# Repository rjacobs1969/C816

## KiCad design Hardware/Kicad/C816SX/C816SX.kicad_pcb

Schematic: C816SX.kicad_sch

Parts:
C1, C2: 1uF; C_0603_1608Metric
C6, C8: 2.2uF; C_0603_1608Metric
C10, C11: 10uF; C_0805_2012Metric
C22, C23, C24, C25, C26, C27, C28, C29, C30, C31, C32, C33, C34, C35, C36, C37, C38, C39, C40, C41, C42, C43, C44, C45, C48, C49, C50: 100n; C_0402_1005Metric
C46, C47: 2.2n; C_0402_1005Metric
D1: LED; LED_D5.0mm_Horizontal_O6.35mm_Z3.0mm
H5, H6, H7, H8: MountingHole; MountingHole_3.5mm
IC4: IS61WV20488FBLL-10TLI; SOP80P1176X120-44N; Mouser Part Number 870-61W20488FBLL10TI
J1: Conn_02x06_Odd_Even; PinHeader_2x06_P2.54mm_Vertical
J2: HDMI_A; HDMI_A_Molex_208658-1001_Horizontal
J4: USB_A_Stacked; USB_A_Wuerth_61400826021_Horizontal_Stacked
J5, J9: DE9_Pins; DSUB-9_Pins_Horizontal_P2.77x2.84mm_EdgePinOffset4.94mm_Hou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
J10: 5749265-1; 57492651; Mouser Part Number 571-5749265-1
J11: Conn_02x06_Odd_Even; PinSocket_2x06_P2.54mm_Vertical
J14, J15, J19, J20: Conn_02x03_Odd_Even; PinHeader_2x03_P2.54mm_Vertical
J16: Conn_01x06_Pin; PinSocket_1x06_P2.54mm_Vertical
J17: Conn_01x09; PinSocket_1x09_P2.54mm_Vertical
J18: USB_B; USB_B_Lumberg_2411_02_Horizontal
J21: SD_Card_Receptacle; SD_TE_2041021
J22, J23: Conn_01x07_Pin; PinSocket_1x07_P2.54mm_Vertical
J25: Conn_01x02; JST_EH_B2B-EH-A_1x02_P2.50mm_Vertical
J26, J27: NYS354; Mouser Part Number 568-NYS354
NT23, NT24, NT25, NT26, NT27, NT28, NT29, NT30, NT31, NT32, NT33, NT34, NT35, NT36, NT37, NT38, NT39, NT40, NT42, NT43, NT44, NT45, NT48, NT51, NT52, NT53, NT54, NT55, NT56, NT57, NT58, NT59, NT60, NT61, NT62, NT63, NT64, NT65, NT66, NT67, NT68, NT69: NetTie_2; MyNetTie-2_SMD_Pad0.25mm
R15: 3K3; R_0805_2012Metric_Pad1.20x1.40mm_HandSolder
R20, R41, R42, R43, R44: 1K; R_0402_1005Metric
R25, R26, R28, R29, R32, R34: 1k; R_0603_1608Metric
R27: 330; R_0603_1608Metric
R30, R31: 470; R_0603_1608Metric
R33: 330; R_0805_2012Metric_Pad1.20x1.40mm_HandSolder
R35: 1k5; R_0603_1608Metric
RN4, RN6, RN7, RN8, RN9, RN10, RN11, RN12, RN18, RN20: 33; R_Array_Convex_4x0603
RN13, RN14, RN15, RN16, RN19: 10k; R_Array_Convex_4x0603
RN17: 1k; R_Array_Convex_4x0603
SLOT1: DDR3_204P_SMD; DDR3-SMD_0705F0BE40F
SW1: SW_DIP_x04; SW_DIP_SPSTx04_Piano_10.8x11.72mm_W7.62mm_P2.54mm
U1: W65C816SxQ; LQFP-44_10x10mm_P0.8mm
U2: PCM5102A; TSSOP-20_4.4x6.5mm_P0.65mm
U3: XC6206PxxxMR; SOT-23-3
U4, U7: 74LVC07; SOIC-14_3.9x8.7mm_P1.27mm
U8: W65C22SxQ; LQFP-44_10x10mm_P0.8mm
U14: W25Q128JVS; SOIC-8_5.3x5.3mm_P1.27mm
U15, U17, U18, U19, U20, U21, U22: SN74LVC8T245PWR; TSSOP-24_4.4x7.8mm_P0.65mm; LCSC C27643
Y2: SiT8008xx-7x-xxE; Oscillator_SMD_SiT_PQFN-4Pin_2.0x1.6mm

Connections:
+3V3: C23.1, C25.2, C27.1, C29.1, C30.1, C31.1, C40.1, C41.1, C42.1, C48.1, C49.1, C50.1, IC4.11 (VDD_1), IC4.33 (VDD_2), J16.1, J19.1, J20.6, R15.1, R25.2, R26.2, R28.2, R29.1, R34.1, RN17.1 (R1.1), RN17.2 (R2.1), SLOT1.22, SLOT1.24, U2.1 (CPVDD), U2.20 (DVDD), U4.14 (VCC), U7.14 (VCC), U14.8 (VCC), U15.23 (VccB), U15.24 (VccB), U17.23 (VccB), U17.24 (VccB), U18.23 (VccB), U18.24 (VccB), U19.23 (VccB), U19.24 (VccB), U20.23 (VccB), U20.24 (VccB), U22.23 (VccB), U22.24 (VccB), Y2.1 (OE), Y2.4 (Vdd)
/A0: U1.4 (A0), U18.4 (A2), U22.17 (B5)
/A1: U1.5 (A1), U18.6 (A4), U22.16 (B6)
/A2: U1.7 (A2), U18.8 (A6), U22.15 (B7)
/A3: U1.8 (A3), U18.10 (A8), U22.14 (B8)
/A4: U1.9 (A4), U19.3 (A1)
/A5: U1.10 (A5), U19.4 (A2)
/A6: U1.11 (A6), U19.5 (A3)
/A7: U1.12 (A7), U19.6 (A4)
/A8: U1.13 (A8), U19.7 (A5)
/A9: U1.14 (A9), U19.8 (A6)
/A9_IOL27A: SLOT1.148
/A10: U1.15 (A10), U19.9 (A7)
/A11: U1.16 (A11), U19.10 (A8)
/A11_IOL15A: NT36.1, SLOT1.131
/A12: U1.19 (A12), U18.9 (A7)
/A12_IOL13B: NT27.2, SLOT1.123
/A13: U1.20 (A13), U18.7 (A5)
/A13_IOR32A_READY: IC4.38 (A15), SLOT1.98
/A14: U1.21 (A14), U18.5 (A3)
/A14_IOL8B: NT43.2, SLOT1.113
/A15: U1.22 (A15), U18.3 (A1)
/A15_IOL2B: NT42.2, SLOT1.107
/AGND: C1.2, C8.2, C43.2, C46.2, C47.2, J26.MH1, J26.MH2, J26.MH3, J27.MH1, J27.MH2, J27.MH3, NT67.2, U2.9 (AGND), U3.1 (GND)
/AVDD: C1.1, C43.1, U2.8 (AVDD), U3.2 (VO)
/A_0: IC4.4 (A1), NT43.1, RN6.3 (R3.1)
/A_1: IC4.6 (A3), NT44.1, RN6.1 (R1.1)
/A_2: IC4.16 (A5), NT45.1, RN7.3 (R3.1)
/A_3: IC4.18 (A7), NT37.2, RN7.1 (R1.1)
/A_4: IC4.19 (A8), NT29.1, RN8.4 (R4.1)
/A_5: IC4.20 (A9), NT33.1, RN8.3 (R3.1)
/A_6: IC4.30 (A14), NT28.1, RN8.2 (R2.1)
/A_7: IC4.29 (A13), NT32.1, RN8.1 (R1.1)
/A_8: IC4.28 (A12), NT27.1, RN9.4 (R4.1)
/A_9: IC4.27 (A11), NT31.1, RN9.3 (R3.1)
/A_10: IC4.26 (A10), NT26.1, RN9.2 (R2.1)
/A_11: IC4.25 (A19), NT30.1, RN9.1 (R1.1)
/A_12: IC4.17 (A6), NT36.2, RN7.2 (R2.1)
/A_13: IC4.7 (A4), NT35.2, RN7.4 (R4.1)
/A_14: IC4.5 (A2), NT34.2, RN6.2 (R2.1)
/A_15: IC4.3 (A0), NT42.1, RN6.4 (R4.1)
/B10_IOR31B_~RECFG: SLOT1.96
/B11_IOL13A: NT31.2, SLOT1.129
/B12_IOL7B: NT35.1, SLOT1.121
/B13_IOL8A: NT34.1, SLOT1.115
/B14_IOL2A: IC4.40 (A17), SLOT1.109
/BE: J17.5, RN13.8 (R1.2), U1.34 (BE), U4.2
/BE.: NT54.2, RN14.8 (R1.2), U4.1
/C7_IOL40B_1V5: SLOT1.157
/C9_IOL27B: SLOT1.146
/C10_IOR39A: NT37.1, SLOT1.135
/C11_IOL15B: NT45.2, SLOT1.125
/C12_IOL7A: NT44.2, SLOT1.119
/C13_IOR32B_DONE: NT48.2, SLOT1.136
/CA1: J20.3, RN16.8 (R1.2), U8.38 (CA1)
/CA2: J20.4, RN16.7 (R2.2), U8.37 (CA2)
/CB1: J1.11, U8.13 (CB1)
/CB2: J1.12, U8.14 (CB2)
/CLKVIA: NT68.1, U17.15 (B7)
/CLK_IN: SLOT1.81, Y2.3 (OUT)
/D0: U1.30 (D0), U20.3 (A1), U21.21 (B1)
/D1: U1.29 (D1), U20.4 (A2), U21.20 (B2)
/D2: U1.28 (D2), U20.5 (A3), U21.19 (B3)
/D3: U1.27 (D3), U20.6 (A4), U21.18 (B4)
/D4: U1.26 (D4), U20.7 (A5), U21.17 (B5)
/D5: U1.25 (D5), U20.8 (A6), U21.16 (B6)
/D6: U1.24 (D6), U20.9 (A7), U21.15 (B7)
/D7: U1.23 (D7), U20.10 (A8), U21.14 (B8)
/D7_IOL53B_1V5: SLOT1.159
/D10_IOL17A: SLOT1.182, U7.11
/D11_IOL22A: SLOT1.180, U7.3
/DATADIR: RN4.8 (R1.2), U20.2 (DIR)
/DEMP: U2.10 (DEMP)
/E: U1.33 (E), U4.13, U15.9 (A7)
/E8_IOL45B_1V5: SLOT1.160, SW1.7
/E9_IOL38B_1V5: SLOT1.158, SW1.6
/E10_IOL17B: R28.1, RN17.7 (R2.2), SLOT1.186, U7.12
/E.: NT59.1, U15.15 (B7)
/EPS_CTS: J23.3, NT38.2
/ESP_3V3: C22.2, J21.4 (VDD), J22.3
/ESP_CARD: J21.10 (CARD_DETECT), NT39.2
/ESP_CS: J21.1 (CD/DAT3), J23.4
/ESP_MISO: J21.7 (DAT0), J22.5
/ESP_MOSI: J21.2 (CMD), J22.4
/ESP_RTS: J23.2, NT25.2
/ESP_RX: J22.7, NT23.1
/ESP_SCK: J21.5 (CLK), J22.6
/ESP_SCL: J19.3, J23.6, R26.1
/ESP_SDA: J19.4, J23.5, R25.1
/ESP_STATUS: D1.2 (A), J23.1
/ESP_TX: J23.7, NT24.2
/ESP_WP: J21.11 (WRITE_PROTECT), NT40.2
/F10_IOL11A: R29.2, RN17.8 (R1.2), SLOT1.176, U7.2
/F14_IOT9A: IC4.13 (I/O2), RN11.2 (R2.1), SLOT1.95
/F16_IOT9B: IC4.14 (I/O3), RN11.1 (R1.1), SLOT1.97
/FLT: U2.11 (FLT)
/FMT: U2.16 (FMT)
/F_VCCO0&1: SLOT1.164, SLOT1.166
/F_VCCO7: SLOT1.170, SLOT1.174
/G14_IOT13B: IC4.32 (I/O5), RN10.2 (R2.1), SLOT1.89
/G15_IOT13A: IC4.31 (I/O4), RN10.1 (R1.1), SLOT1.91
/I2S_BCK: RN12.7 (R2.2), U2.13 (BCK)
/I2S_DIN: RN12.6 (R3.2), U2.14 (DIN)
/I2S_LRCK: RN12.5 (R4.2), U2.15 (LRCK)
/JTAG_TCK: J11.6, SLOT1.149
/JTAG_TDI: J11.8, SLOT1.153
/JTAG_TDO: J11.10, SLOT1.147
/JTAG_TMS: J11.12, SLOT1.143
/L: C47.1, J26.1, R30.1
/LVDS_IOR11_N: IC4.15 (WE#), SLOT1.65, U15.14 (B8)
/LVDS_IOR11_P: SLOT1.63
/LVDS_IOR17_N: RN12.3 (R3.1), SLOT1.59
/LVDS_IOR17_P: RN12.2 (R2.1), SLOT1.57
/LVDS_IOR20_N: SLOT1.69, U17.16 (B6)
/LVDS_IOR20_P: IC4.8 (CS#), SLOT1.67
/LVDS_IOR24_N: NT61.2, SLOT1.51
/LVDS_IOR24_P: NT62.2, SLOT1.53
/LVDS_IOR29_N: J2.6 (D1-), SLOT1.35
/LVDS_IOR29_P: J2.4 (D1+), SLOT1.33
/LVDS_IOR38_N: SLOT1.47
/LVDS_IOR38_P: SLOT1.45
/LVDS_IOR40_N: NT32.2, SLOT1.193
/LVDS_IOR40_P: NT28.2, SLOT1.191
/LVDS_IOR42_N: SLOT1.39
/LVDS_IOR42_P: SLOT1.41
/LVDS_IOR44_N: RN18.1 (R1.1), SLOT1.200
/LVDS_IOR44_P: RN18.2 (R2.1), SLOT1.198
/LVDS_IOR49_N: RN18.3 (R3.1), SLOT1.194
/LVDS_IOR49_P: RN18.4 (R4.1), SLOT1.192
/LVDS_IOR53_N: J2.1 (D2+), SLOT1.27
/LVDS_IOR53_P: J2.3 (D2-), SLOT1.29
/LVDS_IOT8_N: IC4.35 (I/O6), RN10.3 (R3.1), SLOT1.79
/LVDS_IOT8_P: IC4.36 (I/O7), RN10.4 (R4.1), SLOT1.77
/LVDS_IOT14_N: NT69.2, SLOT1.90
/LVDS_IOT14_P: NT68.2, SLOT1.92
/LVDS_IOT18_N: NT51.1, SLOT1.86
/LVDS_IOT18_P: NT66.1, SLOT1.84
/LVDS_IOT22_N: IC4.10 (I/O1), RN11.3 (R3.1), SLOT1.85
/LVDS_IOT22_P: IC4.9 (I/O0), RN11.4 (R4.1), SLOT1.83
/LVDS_IOT32_N: RN20.1 (R1.1), SLOT1.152
/LVDS_IOT32_P: RN20.2 (R2.1), SLOT1.154
/LVDS_IOT36_N: NT65.1, SLOT1.78
/LVDS_IOT36_P: IC4.39 (A16), SLOT1.80
/LVDS_IOT38_N: NT64.1, SLOT1.74
/LVDS_IOT38_P: RN12.4 (R4.1), SLOT1.76
/LVDS_IOT40_N: IC4.37 (OE#), SLOT1.73
/LVDS_IOT40_P: SLOT1.75, U17.14 (B8)
/LVDS_IOT44_N: IC4.42 (A20), SLOT1.101
/LVDS_IOT44_P: IC4.41 (A18), SLOT1.103
/LVDS_RX1_N: NT63.1, SLOT1.50
/LVDS_RX1_P: NT55.1, SLOT1.52
/LVDS_RX2_N: SLOT1.46
/LVDS_RX2_P: SLOT1.44
/LVDS_RX3_N: SLOT1.42
/LVDS_RX3_P: SLOT1.40
/LVDS_RX4_N: J2.9 (D0-), SLOT1.34
/LVDS_RX4_P: J2.7 (D0+), SLOT1.36
/LVDS_RX5_N: J2.12 (CK-), SLOT1.28
/LVDS_RX5_P: J2.10 (CK+), SLOT1.30
/LVDS_TX1_N: NT23.2, SLOT1.142
/LVDS_TX1_P: NT38.1, SLOT1.140
/LVDS_TX2_N: NT25.1, SLOT1.132
/LVDS_TX2_P: NT24.1, SLOT1.130
/LVDS_TX3_N: NT60.2, SLOT1.70
/LVDS_TX3_P: NT59.2, SLOT1.68
/LVDS_TX4_N: NT58.1, SLOT1.62
/LVDS_TX4_P: NT53.1, SLOT1.64
/LVDS_TX5_N: NT57.1, SLOT1.56
/LVDS_TX5_P: NT56.1, SLOT1.58
/M11_IOR27B_FPGA_TXO: J11.7, SLOT1.11
/MISO: J16.5, NT66.2, U14.2 (DO/IO_{1})
/MOSI: J16.3, NT64.2, U14.5 (DI/IO_{0})
/MX: U1.36 (MX)
/N6_IOR51A: NT30.2, SLOT1.175
/N7_IOR47B: NT26.2, SLOT1.177
/N9_IOR36B: NT29.2, SLOT1.181
/PA0: J9.1, J20.1, RN16.6 (R3.2), U8.40 (PA0)
/PA1: J9.2, J20.2, RN16.5 (R4.2), U8.41 (PA1)
/PA2: J9.3, J14.3, J15.3, RN15.7 (R2.2), U8.42 (PA2)
/PA3: J9.4, J14.1, J15.1, RN15.8 (R1.2), U8.43 (PA3)
/PA4: J9.6, J14.4, RN19.8 (R1.2), U8.44 (PA4)
/PA5: J9.5, J14.5, RN19.7 (R2.2), U8.1 (PA5)
/PA6: J9.9, J15.4, RN15.6 (R3.2), U8.2 (PA6)
/PA7: J15.5, RN15.5 (R4.2), U8.3 (PA7)
/PB0: J1.3, J5.1, U8.4 (PB0)
/PB1: J1.4, J5.2, U8.6 (PB1)
/PB2: J1.5, J5.3, U8.7 (PB2)
/PB3: J1.6, J5.4, U8.8 (PB3)
/PB4: J1.7, J5.6, U8.9 (PB4)
/PB5: J1.8, J5.5, U8.10 (PB5)
/PB6: J1.9, J5.9, U8.11 (PB6)
/PB7: J1.10, R33.1, U8.12 (PB7)
/PHI2: RN4.6 (R3.2), U1.35 (ϕ0)
/PHI2.2: RN4.7 (R2.2), U8.21 (ϕ2)
/PS2DAT: J10.1, RN17.5 (R4.2), U7.10, U7.13
/PSCLK: J10.5, RN17.6 (R3.2), U7.1, U7.4
/PULLUP: J20.5, RN19.5 (R4.2), RN19.6 (R3.2)
/R: C46.1, J27.1, R31.1
/R9_IOR35A: NT33.2, SLOT1.183
/RDY: R44.2, U1.41 (RDY), U15.5 (A3)
/RDY.: NT53.2, U15.19 (B3), U17.21 (B1)
/RS0: U8.36 (RS0), U22.7 (A5)
/RS1: U8.35 (RS1), U22.8 (A6)
/RS2: U8.34 (RS2), U22.9 (A7)
/RS3: U8.33 (RS3), U22.10 (A8)
/RW: NT52.1, U1.32 (R/~W), U15.10 (A8), U22.18 (B4)
/SCK: J16.4, NT65.2, U14.6 (CLK)
/T2_IOB48B_1V5: SLOT1.163
/T3_IOB52B_1V5: NT40.1, SLOT1.165
/T4_IOB45B_1V5: SLOT1.169, SW1.8
/T5_IOB54B_1V5: NT39.1, SLOT1.171
/T10_IOR35B_FPGA_~RST: SLOT1.15
/T13_IOR8B_FPGA_RXO: J11.5, SLOT1.1
/UD1N: J4.2 (D1-), RN18.6 (R3.2)
/UD1P: J4.3 (D1+), RN18.5 (R4.2)
/UD2N: J4.6 (D2-), RN18.8 (R1.2)
/UD2P: J4.7 (D2+), RN18.7 (R2.2)
/UD3N: J18.2 (D-), RN20.8 (R1.2)
/UD3P: J18.3 (D+), RN20.6 (R3.2), RN20.7 (R2.2)
/USB3_CON: NT48.1, R35.2
/VBUS: J5.7, J9.7
/VD0: U8.30 (D0), U21.3 (A1)
/VD1: U8.29 (D1), U21.4 (A2)
/VD2: U8.28 (D2), U21.5 (A3)
/VD3: U8.26 (D3), U21.6 (A4)
/VD4: U8.25 (D4), U21.7 (A5)
/VD5: U8.24 (D5), U21.8 (A6)
/VD6: U8.23 (D6), U21.9 (A7)
/VD7: U8.22 (D7), U21.10 (A8)
/VDA: U1.37 (VDA), U15.7 (A5)
/VDA.: NT61.1, U15.17 (B5)
/VPA: U1.2 (VPA), U15.8 (A6)
/VPA.: NT60.1, U15.16 (B6)
/XSMT: U2.17 (XSMT)
/_816: J17.2, U4.12
/_ABT: J17.7, RN13.6 (R3.2), U1.42 (~ABORT), U4.10
/_ABT.: NT56.2, U4.11
/_CESD: J16.2, NT63.2
/_CS2_VIA: RN4.5 (R4.2), U8.19 (~CS2), U21.22 (~OE)
/_CSFLASH: NT51.2, U14.1 (~CS)
/_CSVIA: NT69.1, U17.17 (B5)
/_IRQ: J17.6, RN13.7 (R2.2), U1.43 (~IRQ), U4.8, U7.6
/_IRQ.: NT58.2, U4.9
/_IRQ.2: R32.2, U7.5, U8.17 (~IRQ)
/_NMI: J17.8, RN13.5 (R4.2), U1.1 (~NMI), U4.6
/_NMI.: NT57.2, U4.5
/_RESET: J17.3, RN14.5 (R4.2), U1.38 (~RES), U4.4, U8.31 (~RES)
/_RESET.: NT54.1, NT55.2, U4.3
/_RWVIA: U8.18 (R/~W), U22.6 (A4)
/_VP: U1.40 (~VP), U15.6 (A4)
/_VP.: NT62.1, U15.18 (B4)
/_WE: NT52.2, U21.2 (DIR)
/_WPFLASH: R15.2, SW1.5, U14.3 (~WP/IO_{2})
GND: C2.2, C10.2, C11.2, C22.1, C23.2, C24.1, C25.1, C26.2, C27.2, C28.2, C29.2, C30.2, C31.2, C32.2, C33.2, C34.2, C35.2, C36.2, C37.2, C38.2, C39.2, C40.2, C41.2, C42.2, C44.2, C45.2, C48.2, C49.2, C50.2, IC4.12 (VSS_1), IC4.34 (VSS_2), J1.2, J2.2 (D2S), J2.5 (D1S), J2.8 (D0S), J2.11 (CKS), J2.17 (GND), J2.SH, J4.4 (GND1), J4.8 (GND2), J4.SH (Shield), J5.8, J9.8, J10.3, J10.7, J10.8, J10.9, J11.1, J11.2, J14.6, J15.6, J16.6, J17.1, J18.4 (GND), J18.SH (Shield), J19.6, J21.3 (VSS), J21.6 (VSS), J21.SH (SHELL), J22.2, J25.1, NT67.1, R27.2, R41.2, RN12.1 (R1.1), RN14.1 (R1.1), SLOT1.2, SLOT1.3, SLOT1.8, SLOT1.9, SLOT1.13, SLOT1.14, SLOT1.19, SLOT1.20, SLOT1.25, SLOT1.26, SLOT1.31, SLOT1.32, SLOT1.37, SLOT1.38, SLOT1.43, SLOT1.48, SLOT1.49, SLOT1.54, SLOT1.55, SLOT1.60, SLOT1.61, SLOT1.66, SLOT1.71, SLOT1.72, SLOT1.127, SLOT1.128, SLOT1.133, SLOT1.134, SLOT1.138, SLOT1.139, SLOT1.144, SLOT1.145, SLOT1.150, SLOT1.151, SLOT1.155, SLOT1.156, SLOT1.161, SLOT1.162, SLOT1.167, SLOT1.168, SLOT1.172, SLOT1.173, SLOT1.178, SLOT1.179, SLOT1.184, SLOT1.185, SLOT1.189, SLOT1.190, SLOT1.195, SLOT1.196, SLOT1.MP, SW1.1, SW1.2, SW1.3, SW1.4, U1.17 (VSS), U1.18 (VSS), U1.39 (VSS), U2.3 (CPGND), U2.19 (DGND), U4.7 (GND), U7.7 (GND), U7.9, U8.39 (VSS), U14.4 (GND), U15.3 (A1), U15.4 (A2), U15.11 (GND), U15.12 (GND), U15.13 (GND), U15.22 (~OE), U17.11 (GND), U17.12 (GND), U17.13 (GND), U17.22 (~OE), U18.11 (GND), U18.12 (GND), U18.13 (GND), U18.22 (~OE), U19.11 (GND), U19.12 (GND), U19.13 (GND), U19.22 (~OE), U20.11 (GND), U20.12 (GND), U20.13 (GND), U20.22 (~OE), U21.11 (GND), U21.12 (GND), U21.13 (GND), U22.2 (DIR), U22.11 (GND), U22.12 (GND), U22.13 (GND), U22.22 (~OE), Y2.2 (GND)
unnamed: D1.1 (K), R27.1
unnamed: J17.4, R33.2
unnamed: RN4.1 (R1.1), U17.10 (A8)
unnamed: RN4.2 (R2.1), U17.9 (A7)
unnamed: RN4.3 (R3.1), U17.8 (A6)
unnamed: RN4.4 (R4.1), U17.7 (A5)
unnamed: RN6.8 (R1.2), U18.18 (B4)
unnamed: RN6.7 (R2.2), U18.19 (B3)
unnamed: RN6.6 (R3.2), U18.20 (B2)
unnamed: RN6.5 (R4.2), U18.21 (B1)
unnamed: RN7.8 (R1.2), U18.14 (B8)
unnamed: RN7.7 (R2.2), U18.15 (B7)
unnamed: RN7.6 (R3.2), U18.16 (B6)
unnamed: RN7.5 (R4.2), U18.17 (B5)
unnamed: RN8.8 (R1.2), U19.18 (B4)
unnamed: RN8.7 (R2.2), U19.19 (B3)
unnamed: RN8.6 (R3.2), U19.20 (B2)
unnamed: RN8.5 (R4.2), U19.21 (B1)
unnamed: RN9.8 (R1.2), U19.14 (B8)
unnamed: RN9.7 (R2.2), U19.15 (B7)
unnamed: RN9.6 (R3.2), U19.16 (B6)
unnamed: RN9.5 (R4.2), U19.17 (B5)
unnamed: RN10.8 (R1.2), U20.18 (B4)
unnamed: RN10.7 (R2.2), U20.19 (B3)
unnamed: RN10.6 (R3.2), U20.20 (B2)
unnamed: RN10.5 (R4.2), U20.21 (B1)
unnamed: RN11.8 (R1.2), U20.14 (B8)
unnamed: RN11.7 (R2.2), U20.15 (B7)
unnamed: RN11.6 (R3.2), U20.16 (B6)
unnamed: RN11.5 (R4.2), U20.17 (B5)
unnamed: RN12.8 (R1.2), U2.12 (SCK)
unnamed: RN20.3 (R3.1), RN20.4 (R4.1)
unnamed: R35.1, RN20.5 (R4.2)
unnamed: C6.2, U2.4 (CAPM)
unnamed: C6.1, U2.2 (CAPP)
unnamed: C10.1, C45.1, U2.18 (LDOO)
unnamed: R30.2, U2.6 (OUTL)
unnamed: R31.2, U2.7 (OUTR)
unnamed: C8.1, U2.5 (VNEG)
unnamed: R34.2, U14.7 (~HOLD/~RESET/IO_{3})
unnamed: R20.1, U15.2 (DIR)
unnamed: R44.1, U17.3 (A1)
unnamed: R41.1, U17.2 (DIR)
unnamed: R42.1, U18.2 (DIR)
unnamed: R43.1, U19.2 (DIR)
VCC: C2.1, C11.1, C24.2, C26.1, C28.1, C32.1, C33.1, C34.1, C35.1, C36.1, C37.1, C38.1, C39.1, C44.1, J1.1, J2.18 (+5V), J4.1 (VBUS1), J4.5 (VBUS2), J10.4, J14.2, J15.2, J17.9, J22.1, J25.2, R20.2, R32.1, R42.2, R43.2, RN13.1 (R1.1), RN13.2 (R2.1), RN13.3 (R3.1), RN13.4 (R4.1), RN14.4 (R4.1), RN15.1 (R1.1), RN15.2 (R2.1), RN15.3 (R3.1), RN15.4 (R4.1), RN16.1 (R1.1), RN16.2 (R2.1), RN16.3 (R3.1), RN16.4 (R4.1), RN17.3 (R3.1), RN17.4 (R4.1), RN19.1 (R1.1), RN19.2 (R2.1), RN19.3 (R3.1), RN19.4 (R4.1), SLOT1.4, SLOT1.5, SLOT1.6, SLOT1.7, U1.3 (VDD), U1.31 (VDD), U3.3 (VI), U8.15 (VDD), U8.20 (CS1), U15.1 (VccA), U17.1 (VccA), U18.1 (VccA), U19.1 (VccA), U20.1 (VccA), U21.1 (VccA), U21.23 (VccB), U21.24 (VccB), U22.1 (VccA)

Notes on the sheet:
1/IOT4A/K14
LEVEL CONVERTERS
A <--> B
4/IOB54B/T5
2/IOR26B/A6
2/IOR17B/T12
0/IOT22A/J16
0/IOT14A/G11
2/IOR11A/R12
3/IOR40B/L9
1/IOT52B/N14
4/IOB52B/T3
7/IOL13B/A12
A->B
7/IOL11A/F10
3/IOR29A/T7
0/IOT13B/G14
SNES2/3
2/IOR24A/T11
1/IOT54B/R16
0/IOT20B/H16
B -> A
0/IOT6A/E15
3/IOR42B/M6
7/IOL15B/C11
VIA - JOY - SNES
SNES0/1
7/IOL15A/A11
ESP32-C5 mini
Vcc Bank2 = 3.3V
2/IOR24B/P11
7/IOL2A/B14
3/IOR39A/C10
3/IOR53A/P6
4/IOL40B/C7
0/IOT24B/K16
3/IOR44B/L8
_RE
1/IOT54A/P15
7/IOL8A/B13

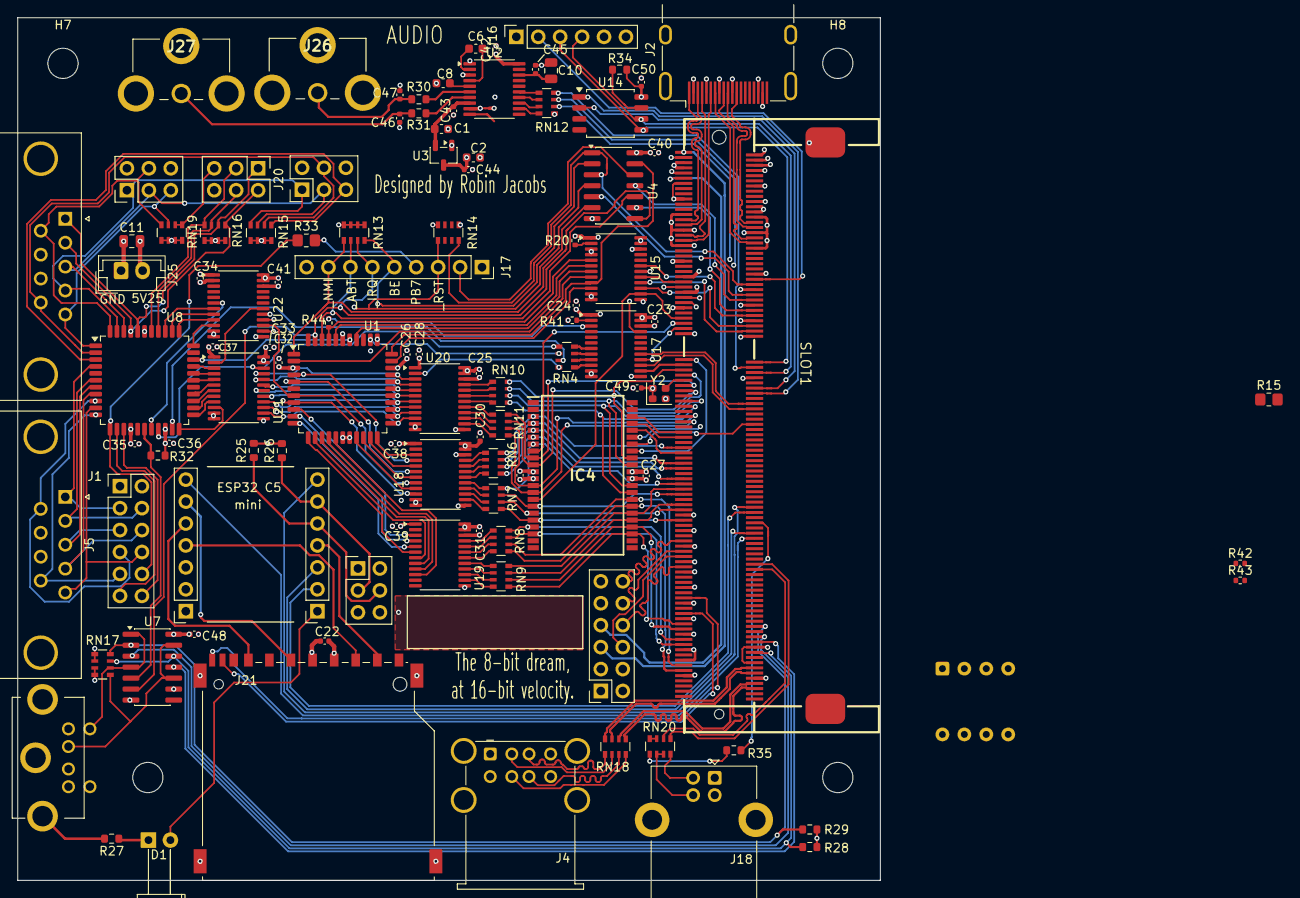
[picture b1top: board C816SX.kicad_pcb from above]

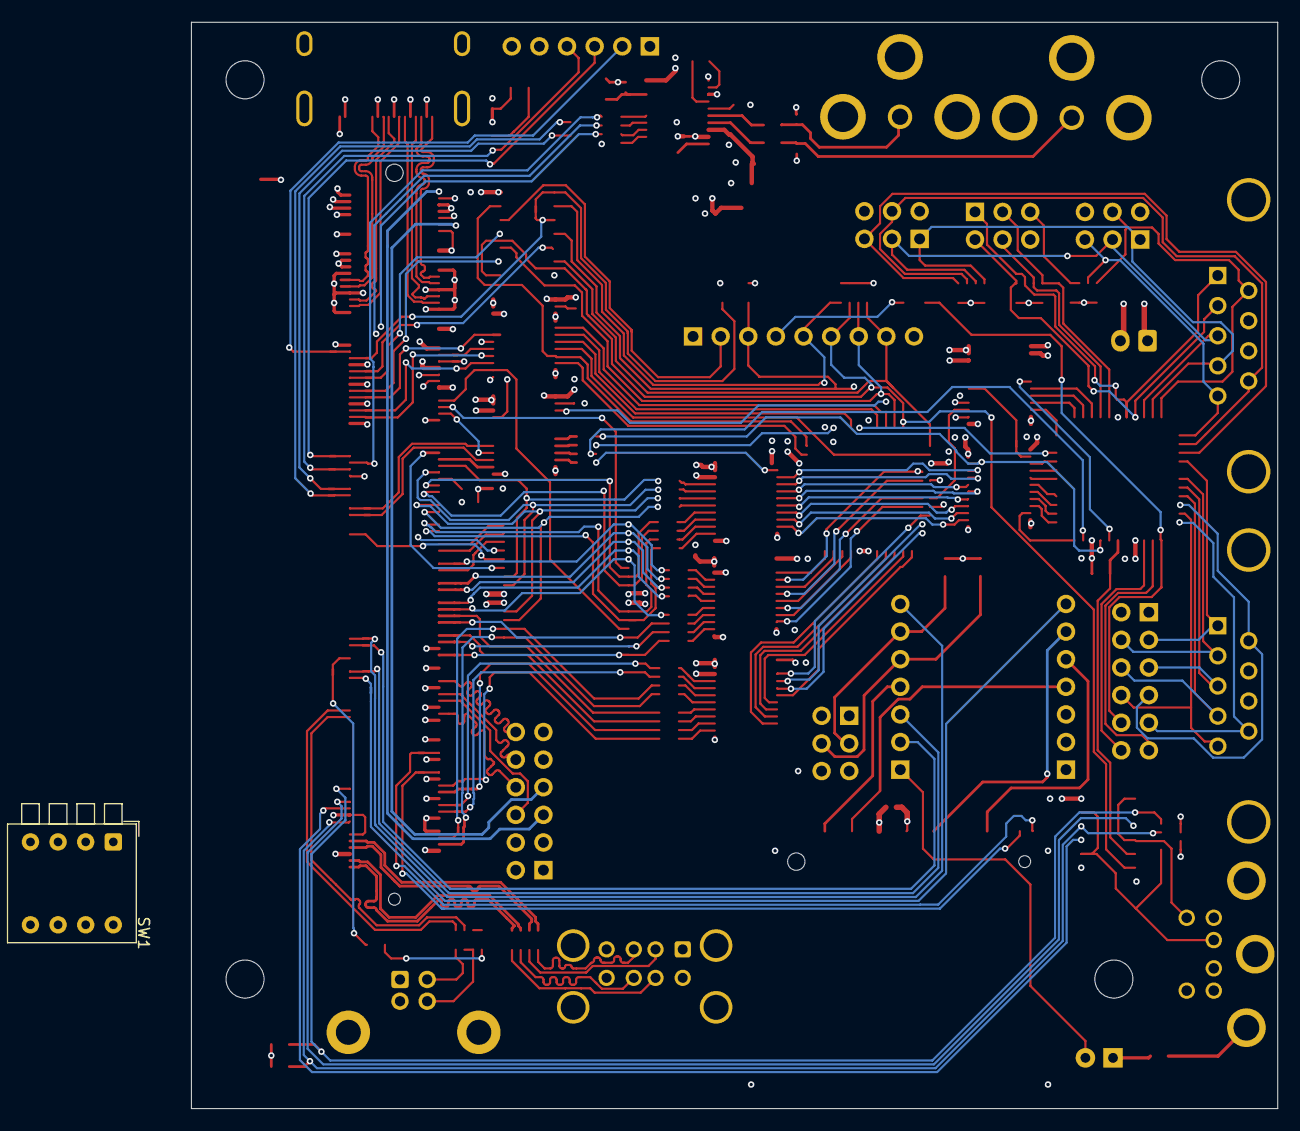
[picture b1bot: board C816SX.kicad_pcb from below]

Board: 6 copper layers, 99.9 x 99.9 mm, 153 parts (2 on the bottom side), 279 nets.

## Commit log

2026-04-19 initial
2026-04-22 C816SX
2026-04-23 ckeanup
